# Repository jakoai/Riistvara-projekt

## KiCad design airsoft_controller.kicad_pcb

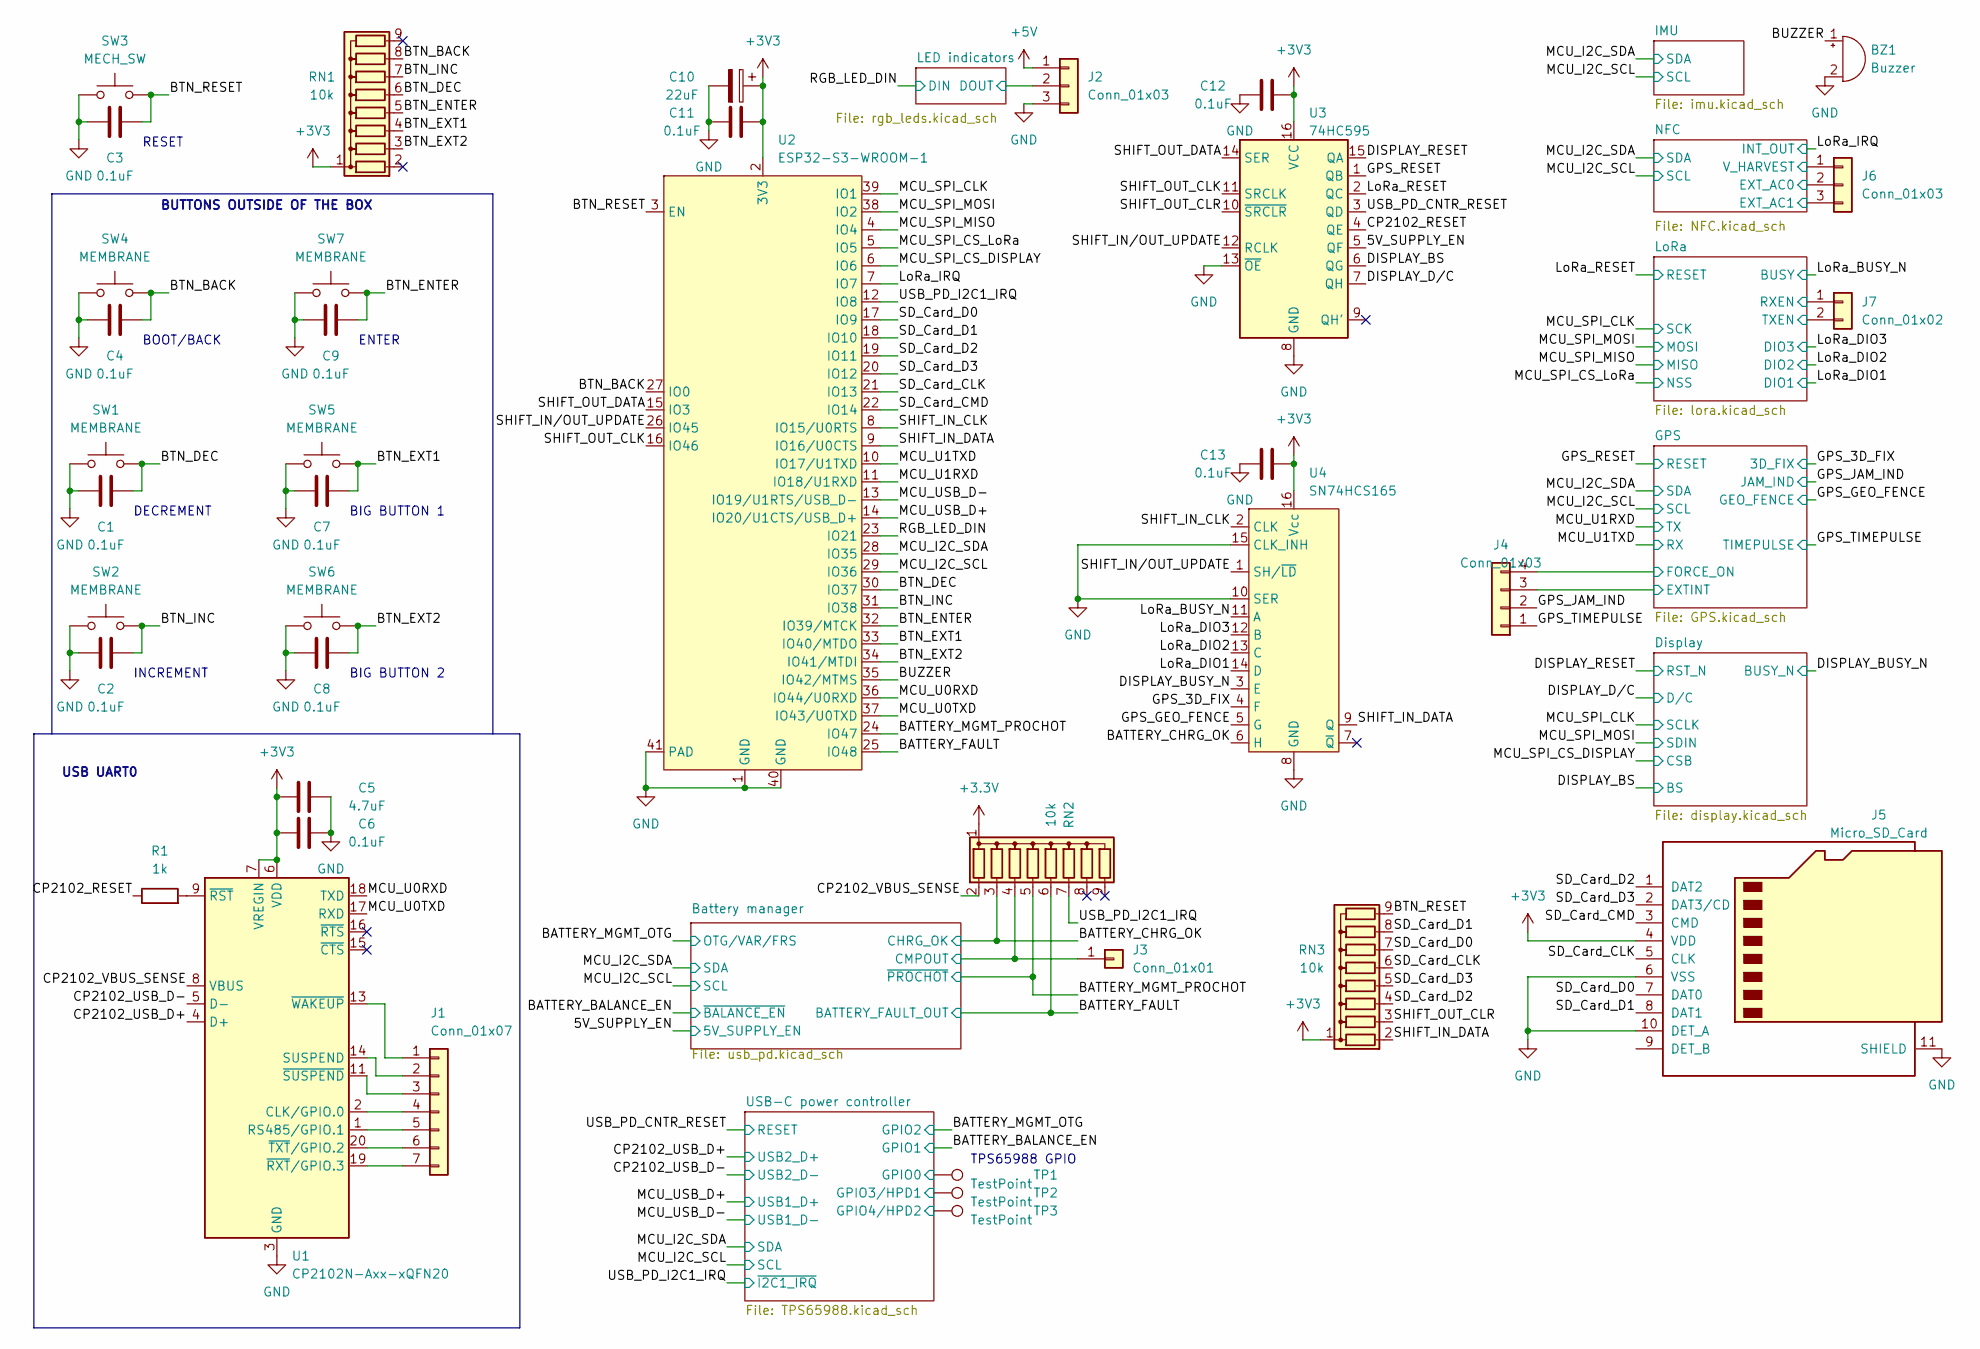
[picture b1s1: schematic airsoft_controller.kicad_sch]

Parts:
BZ1: Buzzer
C1, C2, C3, C4, C6, C7, C8, C9, C11, C12, C13: 0.1uF; C_0603_1608Metric_Pad1.08x0.95mm_HandSolder
C5: 4.7uF; C_0603_1608Metric_Pad1.08x0.95mm_HandSolder
C10: 22uF; CP_Elec_5x5.3
J1: Conn_01x07; PinSocket_1x07_P2.54mm_Vertical
J2, J6: Conn_01x03; PinSocket_1x03_P2.54mm_Vertical
J3: Conn_01x01; PinSocket_1x01_P2.54mm_Vertical
J4: Conn_01x03; PinSocket_1x04_P2.54mm_Vertical
J5: Micro_SD_Card; microSD-W3JA7HH800293
J7: Conn_01x02; PinSocket_1x02_P2.54mm_Vertical
R1: 1k; R_0603_1608Metric_Pad0.98x0.95mm_HandSolder
RN1, RN2, RN3: 10k; R_Array_SIP9
SW1, SW2, SW4, SW5, SW6, SW7: MEMBRANE; SW_rubber_membrane_for_led
SW3: MECH_SW; SWITCH_TL3315NF250Q
TP1, TP2, TP3: TestPoint; TestPoint_Pad_D1.5mm
U1: CP2102N-Axx-xQFN20; SiliconLabs_QFN-20-1EP_3x3mm_P0.5mm_EP1.8x1.8mm
U2: ESP32-S3-WROOM-1; ESP32­S3­WROOM­1
U3: 74HC595; TSSOP-16_4.4x5mm_P0.65mm
U4: SN74HCS165; TSSOP-16_4.4x5mm_P0.65mm

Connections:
+3V3: C5.1, C6.1, C10.1, C11.2, C12.2, C13.2, J5.4 (VDD), RN1.1 (common), RN3.1 (common), U1.6 (VDD), U1.7 (VREGIN), U2.2 (3V3), U3.16 (VCC), U4.16 (Vcc); also elsewhere on the board
+5V: J2.1; also elsewhere on the board
/5V_SUPPLY_EN: U3.5 (QF); also elsewhere on the board
/BATTERY_CHRG_OK: RN2.3 (R2), U4.6 (H); also elsewhere on the board
/BATTERY_FAULT: RN2.6 (R5), U2.25 (IO48); also elsewhere on the board
/BATTERY_MGMT_PROCHOT: RN2.5 (R4), U2.24 (IO47); also elsewhere on the board
/BTN_BACK: C4.1, RN1.8 (R7), SW4.2, U2.27 (IO0)
/BTN_DEC: C1.1, RN1.6 (R5), SW1.2, U2.30 (IO37)
/BTN_ENTER: C9.1, RN1.5 (R4), SW7.2, U2.32 (IO39/MTCK)
/BTN_EXT1: C7.1, RN1.4 (R3), SW5.2, U2.33 (IO40/MTDO)
/BTN_EXT2: C8.1, RN1.3 (R2), SW6.2, U2.34 (IO41/MTDI)
/BTN_INC: C2.1, RN1.7 (R6), SW2.2, U2.31 (IO38)
/BTN_RESET: C3.1, RN3.9 (R8), SW3.3 (B), SW3.4 (B), U2.3 (EN)
/BUZZER: BZ1.1 (-), U2.35 (IO42/MTMS)
/Battery manager/CMPOUT: J3.1, RN2.4 (R3); also elsewhere on the board
/CP2102_RESET: R1.1, U3.4 (QE)
/CP2102_USB_D+: U1.4 (D+); also elsewhere on the board
/CP2102_USB_D-: U1.5 (D-); also elsewhere on the board
/CP2102_VBUS_SENSE: RN2.2 (R1), U1.8 (VBUS)
/DISPLAY_BS: U3.6 (QG); also elsewhere on the board
/DISPLAY_BUSY_N: U4.3 (E); also elsewhere on the board
/DISPLAY_D/C: U3.7 (QH); also elsewhere on the board
/DISPLAY_RESET: U3.15 (QA); also elsewhere on the board
/GPS/EXTINT: J4.3; also elsewhere on the board
/GPS/FORCE_ON: J4.4; also elsewhere on the board
/GPS_3D_FIX: U4.4 (F); also elsewhere on the board
/GPS_GEO_FENCE: U4.5 (G); also elsewhere on the board
/GPS_JAM_IND: J4.2; also elsewhere on the board
/GPS_RESET: U3.1 (QB); also elsewhere on the board
/GPS_TIMEPULSE: J4.1; also elsewhere on the board
/LED indicators/DOUT: J2.2; also elsewhere on the board
/LoRa/RXEN: J7.1; also elsewhere on the board
/LoRa/TXEN: J7.2; also elsewhere on the board
/LoRa_BUSY_N: U4.11 (A); also elsewhere on the board
/LoRa_DIO1: U4.14 (D); also elsewhere on the board
/LoRa_DIO2: U4.13 (C); also elsewhere on the board
/LoRa_DIO3: U4.12 (B); also elsewhere on the board
/LoRa_IRQ: U2.7 (IO7); also elsewhere on the board
/LoRa_RESET: U3.2 (QC); also elsewhere on the board
/MCU_I2C_SCL: U2.29 (IO36); also elsewhere on the board
/MCU_I2C_SDA: U2.28 (IO35); also elsewhere on the board
/MCU_SPI_CLK: U2.39 (IO1); also elsewhere on the board
/MCU_SPI_CS_DISPLAY: U2.6 (IO6); also elsewhere on the board
/MCU_SPI_CS_LoRa: U2.5 (IO5); also elsewhere on the board
/MCU_SPI_MISO: U2.4 (IO4); also elsewhere on the board
/MCU_SPI_MOSI: U2.38 (IO2); also elsewhere on the board
/MCU_U0RXD: U1.18 (TXD), U2.36 (IO44/U0RXD)
/MCU_U0TXD: U1.17 (RXD), U2.37 (IO43/U0TXD)
/MCU_U1RXD: U2.11 (IO18/U1RXD); also elsewhere on the board
/MCU_U1TXD: U2.10 (IO17/U1TXD); also elsewhere on the board
/MCU_USB_D+: U2.14 (IO20/U1CTS/USB_D+); also elsewhere on the board
/MCU_USB_D-: U2.13 (IO19/U1RTS/USB_D-); also elsewhere on the board
/NFC/EXT_AC0: J6.2; also elsewhere on the board
/NFC/EXT_AC1: J6.3; also elsewhere on the board
/NFC/V_HARVEST: J6.1; also elsewhere on the board
/RGB_LED_DIN: U2.23 (IO21); also elsewhere on the board
/SD_Card_CLK: J5.5 (CLK), RN3.6 (R5), U2.21 (IO13)
/SD_Card_CMD: J5.3 (CMD), U2.22 (IO14)
/SD_Card_D0: J5.7 (DAT0), RN3.7 (R6), U2.17 (IO9)
/SD_Card_D1: J5.8 (DAT1), RN3.8 (R7), U2.18 (IO10)
/SD_Card_D2: J5.1 (DAT2), RN3.4 (R3), U2.19 (IO11)
/SD_Card_D3: J5.2 (DAT3/CD), RN3.5 (R4), U2.20 (IO12)
/SHIFT_IN_CLK: U2.8 (IO15/U0RTS), U4.2 (CLK)
/SHIFT_IN_DATA: RN3.2 (R1), U2.9 (IO16/U0CTS), U4.9 (Q)
/SHIFT_IN/OUT_UPDATE: U2.26 (IO45), U3.12 (RCLK), U4.1 (SH/~LD)
/SHIFT_OUT_CLK: U2.16 (IO46), U3.11 (SRCLK)
/SHIFT_OUT_CLR: RN3.3 (R2), U3.10 (~SRCLR)
/SHIFT_OUT_DATA: U2.15 (IO3), U3.14 (SER)
/USB-C power controller/GPIO0: TP1.1; also elsewhere on the board
/USB-C power controller/GPIO3/HPD1: TP2.1; also elsewhere on the board
/USB-C power controller/GPIO4/HPD2: TP3.1; also elsewhere on the board
/USB_PD_CNTR_RESET: U3.3 (QD); also elsewhere on the board
/USB_PD_I2C1_IRQ: RN2.7 (R6), U2.12 (IO8); also elsewhere on the board
GND: BZ1.2 (+), C1.2, C2.2, C3.2, C4.2, C5.2, C6.2, C7.2, C8.2, C9.2, C10.2, C11.1, C12.1, C13.1, J2.3, J5.6 (VSS), J5.10 (DET_A), J5.11 (SHIELD), SW1.1, SW2.1, SW3.1 (A), SW3.2 (A), SW4.1, SW5.1, SW6.1, SW7.1, U1.3 (GND), U1.12 (GND), U1.21 (GND), U2.1 (GND), U2.40 (GND), U2.41 (PAD), U3.8 (GND), U3.13 (~OE), U4.8 (GND), U4.10 (SER), U4.15 (CLK_INH); also elsewhere on the board
unnamed: J1.1, U1.13 (~WAKEUP)
unnamed: J1.2, U1.14 (SUSPEND)
unnamed: J1.3, U1.11 (~SUSPEND)
unnamed: J1.4, U1.2 (CLK/GPIO.0)
unnamed: J1.5, U1.1 (RS485/GPIO.1)
unnamed: J1.6, U1.20 (~TXT/GPIO.2)
unnamed: J1.7, U1.19 (~RXT/GPIO.3)
unnamed: R1.2, U1.9 (~RST)

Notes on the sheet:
BOOT/BACK
ENTER
USB UART0
RESET
DECREMENT
INCREMENT
TPS65988 GPIO
BIG BUTTON 1
BUTTONS OUTSIDE OF THE BOX
BIG BUTTON 2

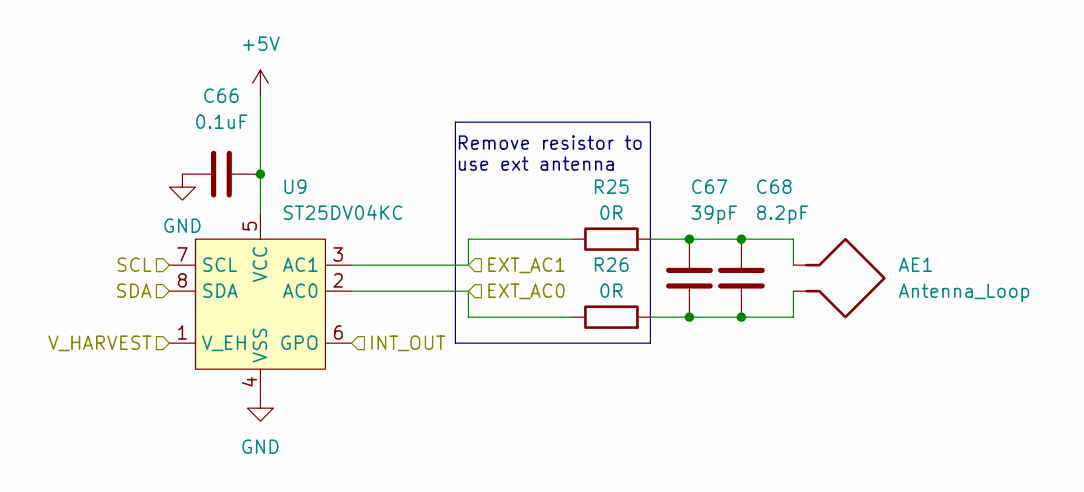
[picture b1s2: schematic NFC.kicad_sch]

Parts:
AE1: Antenna_Loop; Antenna_loop-13.56MHz
C66: 0.1uF; C_0603_1608Metric_Pad1.08x0.95mm_HandSolder
C67: 39pF; C_0603_1608Metric_Pad1.08x0.95mm_HandSolder
C68: 8.2pF; C_0603_1608Metric_Pad1.08x0.95mm_HandSolder
R25, R26: 0R; R_0603_1608Metric_Pad0.98x0.95mm_HandSolder
U9: ST25DV04KC; TSSOP-8_6.4x3mm_P0.65mm

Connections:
+5V: C66.2, U9.5 (VCC); also elsewhere on the board
/LoRa_IRQ: U9.6 (GPO); also elsewhere on the board
/MCU_I2C_SCL: U9.7 (SCL); also elsewhere on the board
/MCU_I2C_SDA: U9.8 (SDA); also elsewhere on the board
/NFC/EXT_AC0: R26.1, U9.2 (AC0); also elsewhere on the board
/NFC/EXT_AC1: R25.1, U9.3 (AC1); also elsewhere on the board
/NFC/V_HARVEST: U9.1 (V_EH); also elsewhere on the board
GND: C66.1, U9.4 (VSS); also elsewhere on the board
unnamed: AE1.1, C67.1, C68.1, R25.2
unnamed: AE1.2, C67.2, C68.2, R26.2

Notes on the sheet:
Remove resistor to use ext antenna

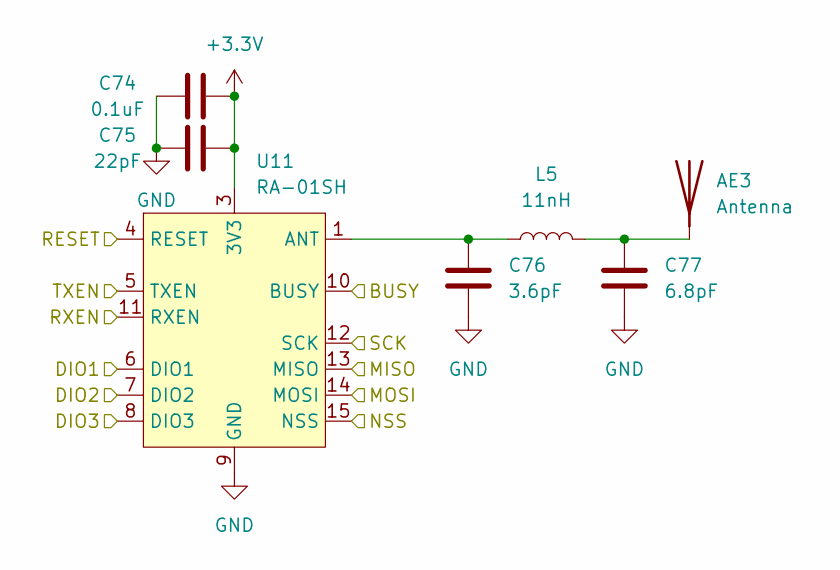
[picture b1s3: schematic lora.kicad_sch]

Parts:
AE3: Antenna; LoRa-antenna-868-HESM
C74: 0.1uF; C_0603_1608Metric_Pad1.08x0.95mm_HandSolder
C75: 22pF; C_0603_1608Metric_Pad1.08x0.95mm_HandSolder
C76: 3.6pF; C_0603_1608Metric_Pad1.08x0.95mm_HandSolder
C77: 6.8pF; C_0603_1608Metric_Pad1.08x0.95mm_HandSolder
L5: 11nH; L_0603_1608Metric_Pad1.05x0.95mm_HandSolder
U11: RA-01SH

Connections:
/LoRa/RXEN: U11.11 (RXEN); also elsewhere on the board
/LoRa/TXEN: U11.5 (TXEN); also elsewhere on the board
/LoRa_BUSY_N: U11.10 (BUSY); also elsewhere on the board
/LoRa_DIO1: U11.6 (DIO1); also elsewhere on the board
/LoRa_DIO2: U11.7 (DIO2); also elsewhere on the board
/LoRa_DIO3: U11.8 (DIO3); also elsewhere on the board
/LoRa_RESET: U11.4 (RESET); also elsewhere on the board
/MCU_SPI_CLK: U11.12 (SCK); also elsewhere on the board
/MCU_SPI_CS_LoRa: U11.15 (NSS); also elsewhere on the board
/MCU_SPI_MISO: U11.13 (MISO); also elsewhere on the board
/MCU_SPI_MOSI: U11.14 (MOSI); also elsewhere on the board
GND: C74.1, C75.1, C76.2, C77.2, U11.2 (GND), U11.9 (GND), U11.16 (GND); also elsewhere on the board
unnamed: AE3.1 (A), C77.1, L5.2
unnamed: C76.1, L5.1, U11.1 (ANT)

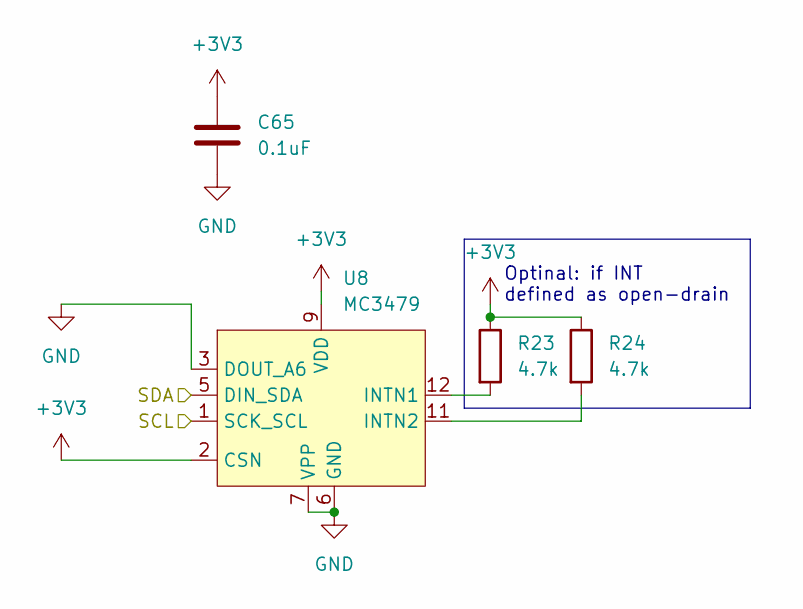
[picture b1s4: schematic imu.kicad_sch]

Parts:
C65: 0.1uF; C_0603_1608Metric_Pad1.08x0.95mm_HandSolder
R23, R24: 4.7k; R_0603_1608Metric_Pad0.98x0.95mm_HandSolder
U8: MC3479; LGA-12_2x2mm_P0.5mm

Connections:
+3V3: C65.2, R23.1, R24.1, U8.2 (CSN), U8.9 (VDD); also elsewhere on the board
/MCU_I2C_SCL: U8.1 (SCK_SCL); also elsewhere on the board
/MCU_I2C_SDA: U8.5 (DIN_SDA); also elsewhere on the board
GND: C65.1, U8.3 (DOUT_A6), U8.6 (GND), U8.7 (VPP); also elsewhere on the board
unnamed: R23.2, U8.12 (INTN1)
unnamed: R24.2, U8.11 (INTN2)

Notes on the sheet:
Optinal: if INT defined as open-drain

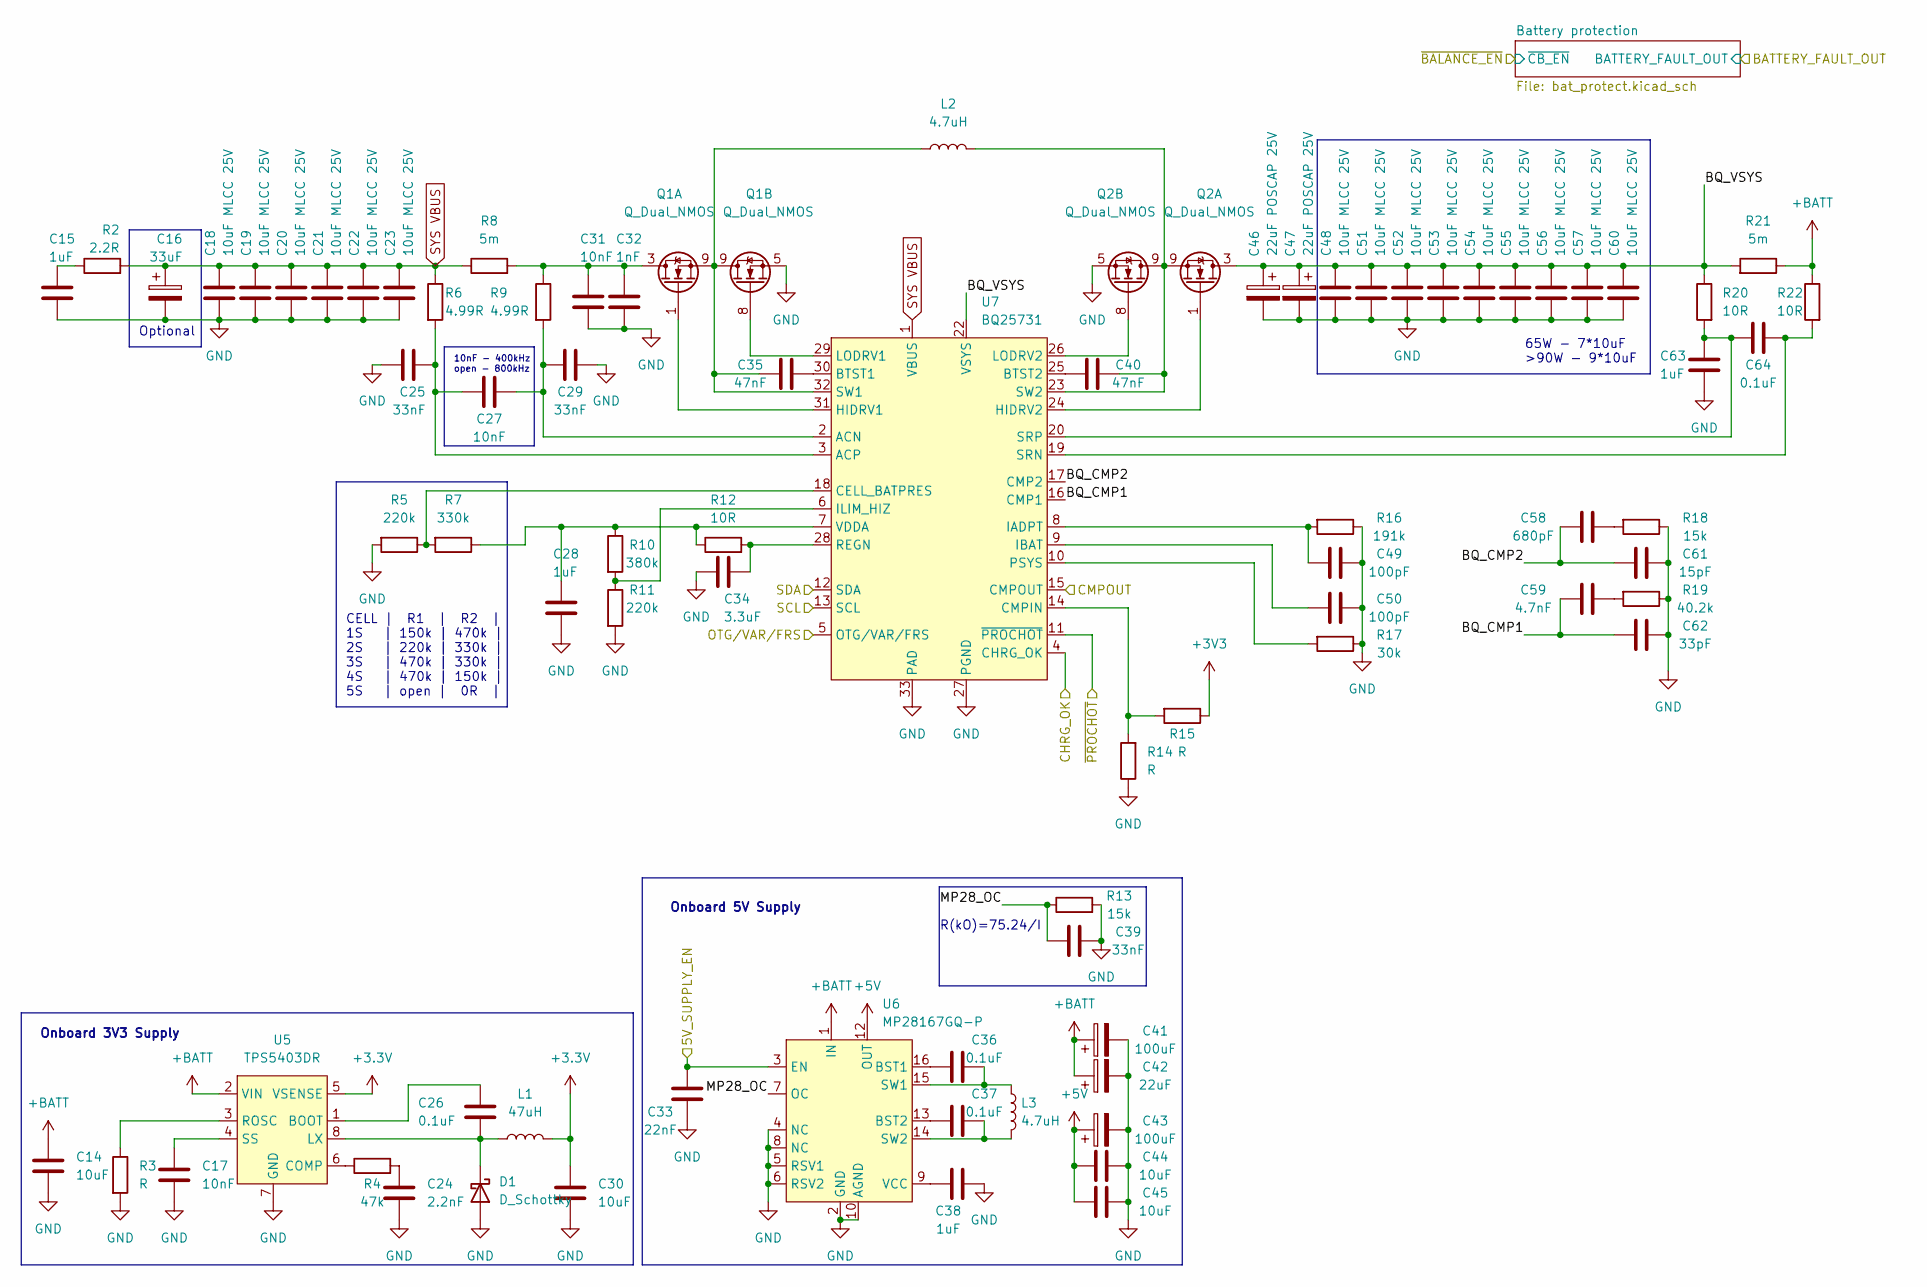
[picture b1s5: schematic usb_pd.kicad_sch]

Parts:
C14, C44, C45: 10uF; C_0805_2012Metric_Pad1.18x1.45mm_HandSolder
C15, C28, C38, C63: 1uF; C_0603_1608Metric_Pad1.08x0.95mm_HandSolder
C16: 33uF; CP_Elec_6.3x5.4
C17, C27, C31: 10nF; C_0603_1608Metric_Pad1.08x0.95mm_HandSolder
C18, C19, C20, C21, C22, C23, C51, C52, C53, C54, C55, C56, C57, C60: 10uF MLCC 25V; C_0805_2012Metric_Pad1.18x1.45mm_HandSolder
C24: 2.2nF; C_0603_1608Metric_Pad1.08x0.95mm_HandSolder
C25, C29, C39: 33nF; C_0603_1608Metric_Pad1.08x0.95mm_HandSolder
C26, C36, C37, C64: 0.1uF; C_0603_1608Metric_Pad1.08x0.95mm_HandSolder
C30: 10uF; C_1206_3216Metric_Pad1.33x1.80mm_HandSolder
C32: 1nF; C_0603_1608Metric_Pad1.08x0.95mm_HandSolder
C33: 22nF; C_0603_1608Metric_Pad1.08x0.95mm_HandSolder
C34: 3.3uF; C_0603_1608Metric_Pad1.08x0.95mm_HandSolder
C35, C40: 47nF; C_0603_1608Metric_Pad1.08x0.95mm_HandSolder
C41, C43: 100uF; CP_Elec_6.3x7.7
C42: 22uF; CP_Elec_5x5.3
C46, C47: 22uF POSCAP 25V; C_1210_3225Metric_Pad1.33x2.70mm_HandSolder
C48: 10uF MLCC 25V; C_1206_3216Metric_Pad1.33x1.80mm_HandSolder
C49, C50: 100pF; C_0603_1608Metric_Pad1.08x0.95mm_HandSolder
C58: 680pF; C_0603_1608Metric_Pad1.08x0.95mm_HandSolder
C59: 4.7nF; C_0603_1608Metric_Pad1.08x0.95mm_HandSolder
C61: 15pF; C_0603_1608Metric_Pad1.08x0.95mm_HandSolder
C62: 33pF; C_0603_1608Metric_Pad1.08x0.95mm_HandSolder
D1: D_Schottky; D_SMB
L1: 47uH; Inductor_104CDMCC
L2: 4.7uH; Inductor_SRP1265C
L3: 4.7uH; Inductor_WLPMA0A040
Q1, Q2: Q_Dual_NMOS; Q_DUAL_NMOS_DMT3006LPB
R2: 2.2R; R_0603_1608Metric_Pad0.98x0.95mm_HandSolder
R3, R14, R15: R; R_0603_1608Metric_Pad0.98x0.95mm_HandSolder
R4: 47k; R_0603_1608Metric_Pad0.98x0.95mm_HandSolder
R5, R11: 220k; R_0603_1608Metric_Pad0.98x0.95mm_HandSolder
R6, R9: 4.99R; R_0603_1608Metric_Pad0.98x0.95mm_HandSolder
R7: 330k; R_0603_1608Metric_Pad0.98x0.95mm_HandSolder
R8, R21: 5m; R_0612_1632Metric_Pad1.18x3.40mm_HandSolder
R10: 380k; R_0603_1608Metric_Pad0.98x0.95mm_HandSolder
R12, R20, R22: 10R; R_0603_1608Metric_Pad0.98x0.95mm_HandSolder
R13, R18: 15k; R_0603_1608Metric_Pad0.98x0.95mm_HandSolder
R16: 191k; R_0603_1608Metric_Pad0.98x0.95mm_HandSolder
R17: 30k; R_0603_1608Metric_Pad0.98x0.95mm_HandSolder
R19: 40.2k; R_0603_1608Metric_Pad0.98x0.95mm_HandSolder
U5: TPS5403DR; SOIC-8_3.9x4.9mm_P1.27mm
U6: MP28167GQ-P; QFN-16
U7: BQ25731; Texas_S-PWQFN-N32_EP2.8x2.8mm

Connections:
+5V: C43.1, C44.1, C45.1, U6.12 (OUT); also elsewhere on the board
+BATT: C14.2, C41.1, C42.1, R21.1, R22.1, U5.2 (VIN), U6.1 (IN); also elsewhere on the board
/5V_SUPPLY_EN: C33.2, U6.3 (EN); also elsewhere on the board
/BATTERY_CHRG_OK: U7.4 (CHRG_OK); also elsewhere on the board
/BATTERY_MGMT_OTG: U7.5 (OTG/VAR/FRS); also elsewhere on the board
/BATTERY_MGMT_PROCHOT: U7.11 (~PROCHOT); also elsewhere on the board
/Battery manager/BQ_CMP1: C59.1, C62.1, U7.16 (CMP1)
/Battery manager/BQ_CMP2: C58.1, C61.1, U7.17 (CMP2)
/Battery manager/BQ_VSYS: C46.1, C47.1, C48.2, C51.2, C52.2, C53.2, C54.2, C55.2, C56.2, C57.2, C60.2, Q2.2 (D1), Q2.3 (D1), Q2.4 (D1), R20.1, R21.2, U7.22 (VSYS)
/Battery manager/CMPOUT: U7.15 (CMPOUT); also elsewhere on the board
/Battery manager/MP28_OC: C39.1, R13.1, U6.7 (OC)
/MCU_I2C_SCL: U7.13 (SCL); also elsewhere on the board
/MCU_I2C_SDA: U7.12 (SDA); also elsewhere on the board
GND: C14.1, C15.1, C16.2, C17.2, C18.1, C19.1, C20.1, C21.1, C22.1, C23.1, C24.2, C25.2, C28.1, C29.2, C30.1, C31.1, C32.1, C33.1, C34.1, C38.2, C39.2, C41.2, C42.2, C43.2, C44.2, C45.2, C46.2, C47.2, C48.1, C49.2, C50.1, C51.1, C52.1, C53.1, C54.1, C55.1, C56.1, C57.1, C60.1, C61.2, C62.2, C63.2, D1.2 (A), Q1.5 (S2), Q1.6 (S2), Q1.7 (S2), Q2.5 (S2), Q2.6 (S2), Q2.7 (S2), R3.2, R5.2, R11.2, R13.2, R14.1, R16.1, R17.1, R18.1, R19.1, U5.7 (GND), U6.2 (GND), U6.4 (NC), U6.5 (RSV1), U6.6 (RSV2), U6.8 (NC), U6.10 (AGND), U6.11 (GND), U7.27 (PGND), U7.33 (PAD); also elsewhere on the board
unnamed: C15.2, R2.1
unnamed: C17.1, U5.4 (SS)
unnamed: C24.1, R4.2
unnamed: C25.1, C27.1, R6.2, U7.3 (ACP)
unnamed: C26.1, U5.1 (BOOT)
unnamed: C26.2, D1.1 (K), L1.1, U5.8 (LX)
unnamed: C27.2, C29.1, R9.2, U7.2 (ACN)
unnamed: C28.2, R7.1, R10.1, R12.1, U7.7 (VDDA)
unnamed: C31.2, C32.2, Q1.2 (D1), Q1.3 (D1), Q1.4 (D1), R8.2, R9.1
unnamed: C34.2, R12.2, U7.28 (REGN)
unnamed: C35.1, U7.30 (BTST1)
unnamed: C35.2, L2.1, Q1.9 (S1/D2), U7.32 (SW1)
unnamed: C36.1, U6.16 (BST1)
unnamed: C36.2, L3.1, U6.15 (SW1)
unnamed: C37.1, U6.13 (BST2)
unnamed: C37.2, L3.2, U6.14 (SW2)
unnamed: C38.1, U6.9 (VCC)
unnamed: C40.1, U7.25 (BTST2)
unnamed: C40.2, L2.2, Q2.9 (S1/D2), U7.23 (SW2)
unnamed: C49.1, R16.2, U7.8 (IADPT)
unnamed: C50.2, U7.9 (IBAT)
unnamed: C58.2, R18.2
unnamed: C59.2, R19.2
unnamed: C63.1, C64.2, R20.2, U7.20 (SRP)
unnamed: C64.1, R22.2, U7.19 (SRN)
unnamed: Q1.1 (G1), U7.31 (HIDRV1)
unnamed: Q1.8 (G2), U7.29 (LODRV1)
unnamed: Q2.1 (G1), U7.24 (HIDRV2)
unnamed: Q2.8 (G2), U7.26 (LODRV2)
unnamed: R3.1, U5.3 (ROSC)
unnamed: R4.1, U5.6 (COMP)
unnamed: R5.1, R7.2, U7.18 (CELL_BATPRES)
unnamed: R10.2, R11.1, U7.6 (ILIM_HIZ)
unnamed: R14.2, R15.2, U7.14 (CMPIN)
unnamed: R17.2, U7.10 (PSYS)
SYS VBUS: C16.1, C18.2, C19.2, C20.2, C21.2, C22.2, C23.2, R2.2, R6.1, R8.1, U7.1 (VBUS); also elsewhere on the board

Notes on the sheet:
65W - 7*10uF >90W - 9*10uF
CELL | R1 | R2 | 1S | 150k | 470k | 2S | 220k | 330k | 3S | 470k | 330k | 4S | 470k | 150k | 5S | open | 0R |
R(kO)=75.24/I
Onboard 3V3 Supply
Optional
10nF - 400kHz open - 800kHz
Onboard 5V Supply

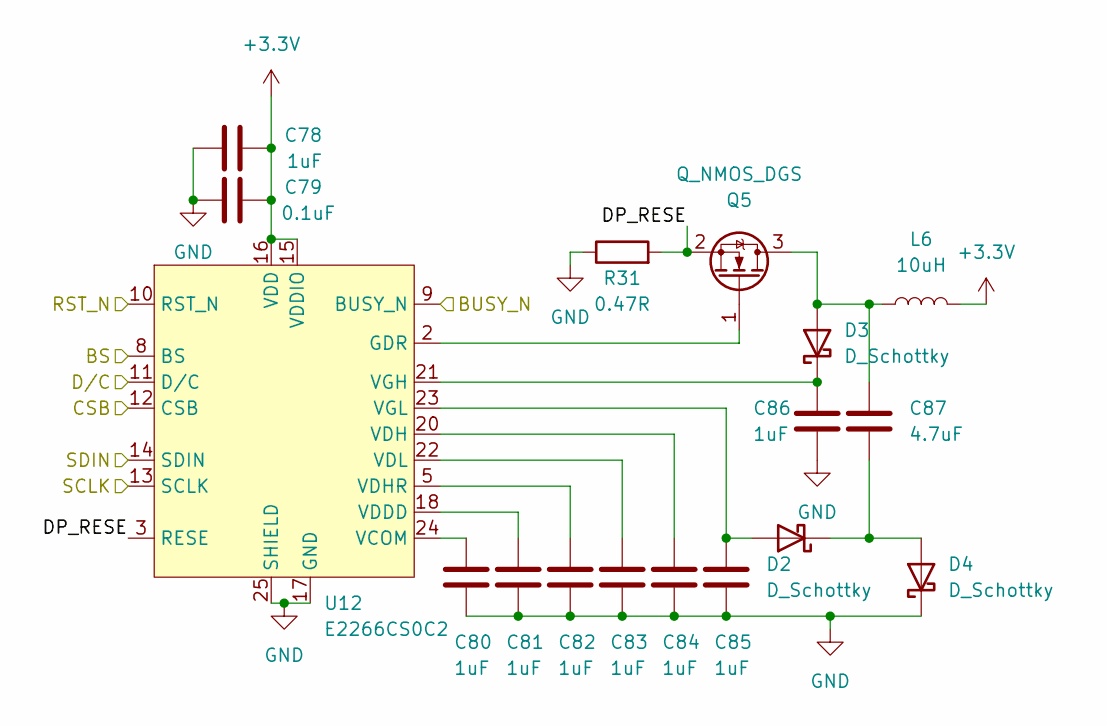
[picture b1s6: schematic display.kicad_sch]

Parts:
C78, C80, C81, C82, C83, C84, C85, C86: 1uF; C_0603_1608Metric_Pad1.08x0.95mm_HandSolder
C79: 0.1uF; C_0603_1608Metric_Pad1.08x0.95mm_HandSolder
C87: 4.7uF; C_0603_1608Metric_Pad1.08x0.95mm_HandSolder
D2, D3, D4: D_Schottky; D-US2H-2
L6: 10uH; L_1210_3225Metric_Pad1.42x2.65mm_HandSolder
Q5: Q_NMOS_DGS; SOT-23
R31: 0.47R; R_0603_1608Metric_Pad0.98x0.95mm_HandSolder
U12: E2266CS0C2; FPC-24p-0.5

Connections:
/DISPLAY_BS: U12.8 (BS); also elsewhere on the board
/DISPLAY_BUSY_N: U12.9 (BUSY_N); also elsewhere on the board
/DISPLAY_D/C: U12.11 (D/C); also elsewhere on the board
/DISPLAY_RESET: U12.10 (RST_N); also elsewhere on the board
/Display/DP_RESE: Q5.2 (S), R31.2, U12.3 (RESE)
/MCU_SPI_CLK: U12.13 (SCLK); also elsewhere on the board
/MCU_SPI_CS_DISPLAY: U12.12 (CSB); also elsewhere on the board
/MCU_SPI_MOSI: U12.14 (SDIN); also elsewhere on the board
GND: C78.2, C79.2, C80.1, C81.1, C82.1, C83.1, C84.1, C85.1, C86.1, D4.1 (K), R31.1, U12.17 (GND), U12.25 (SHIELD), U12.26 (SHIELD); also elsewhere on the board
unnamed: C80.2, U12.24 (VCOM)
unnamed: C81.2, U12.18 (VDDD)
unnamed: C82.2, U12.5 (VDHR)
unnamed: C83.2, U12.22 (VDL)
unnamed: C84.2, U12.20 (VDH)
unnamed: C85.2, D2.2 (A), U12.23 (VGL)
unnamed: C86.2, D3.1 (K), U12.21 (VGH)
unnamed: C87.1, D2.1 (K), D4.2 (A)
unnamed: C87.2, D3.2 (A), L6.1, Q5.3 (D)
unnamed: Q5.1 (G), U12.2 (GDR)

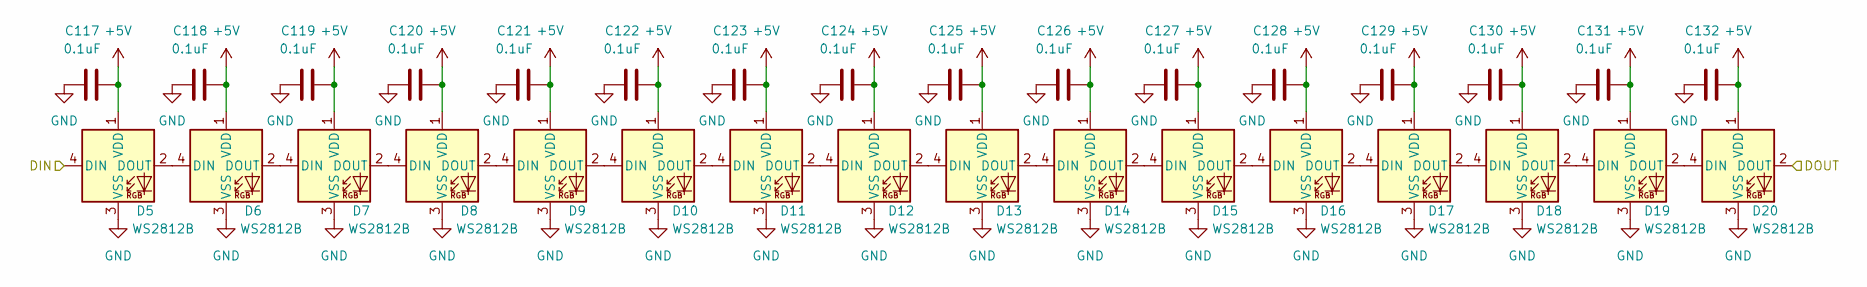
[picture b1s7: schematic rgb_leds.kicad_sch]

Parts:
C117, C118, C119, C120, C121, C122, C123, C124, C125, C126, C127, C128, C129, C130, C131, C132: 0.1uF; C_0603_1608Metric_Pad1.08x0.95mm_HandSolder
D5, D6, D7, D8, D9, D10, D11, D12, D13, D14, D15, D16, D17, D18, D19, D20: WS2812B; LED_WS2812B_PLCC4_5.0x5.0mm_P3.2mm

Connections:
+5V: C117.2, C118.2, C119.2, C120.2, C121.2, C122.2, C123.2, C124.2, C125.2, C126.2, C127.2, C128.2, C129.2, C130.2, C131.2, C132.2, D5.1 (VDD), D6.1 (VDD), D7.1 (VDD), D8.1 (VDD), D9.1 (VDD), D10.1 (VDD), D11.1 (VDD), D12.1 (VDD), D13.1 (VDD), D14.1 (VDD), D15.1 (VDD), D16.1 (VDD), D17.1 (VDD), D18.1 (VDD), D19.1 (VDD), D20.1 (VDD); also elsewhere on the board
/LED indicators/DOUT: D20.2 (DOUT); also elsewhere on the board
/RGB_LED_DIN: D5.4 (DIN); also elsewhere on the board
GND: C117.1, C118.1, C119.1, C120.1, C121.1, C122.1, C123.1, C124.1, C125.1, C126.1, C127.1, C128.1, C129.1, C130.1, C131.1, C132.1, D5.3 (VSS), D6.3 (VSS), D7.3 (VSS), D8.3 (VSS), D9.3 (VSS), D10.3 (VSS), D11.3 (VSS), D12.3 (VSS), D13.3 (VSS), D14.3 (VSS), D15.3 (VSS), D16.3 (VSS), D17.3 (VSS), D18.3 (VSS), D19.3 (VSS), D20.3 (VSS); also elsewhere on the board
unnamed: D5.2 (DOUT), D6.4 (DIN)
unnamed: D6.2 (DOUT), D7.4 (DIN)
unnamed: D7.2 (DOUT), D8.4 (DIN)
unnamed: D8.2 (DOUT), D9.4 (DIN)
unnamed: D10.2 (DOUT), D11.4 (DIN)
unnamed: D9.2 (DOUT), D10.4 (DIN)
unnamed: D11.2 (DOUT), D12.4 (DIN)
unnamed: D12.2 (DOUT), D13.4 (DIN)
unnamed: D13.2 (DOUT), D14.4 (DIN)
unnamed: D14.2 (DOUT), D15.4 (DIN)
unnamed: D15.2 (DOUT), D16.4 (DIN)
unnamed: D16.2 (DOUT), D17.4 (DIN)
unnamed: D17.2 (DOUT), D18.4 (DIN)
unnamed: D19.2 (DOUT), D20.4 (DIN)
unnamed: D18.2 (DOUT), D19.4 (DIN)

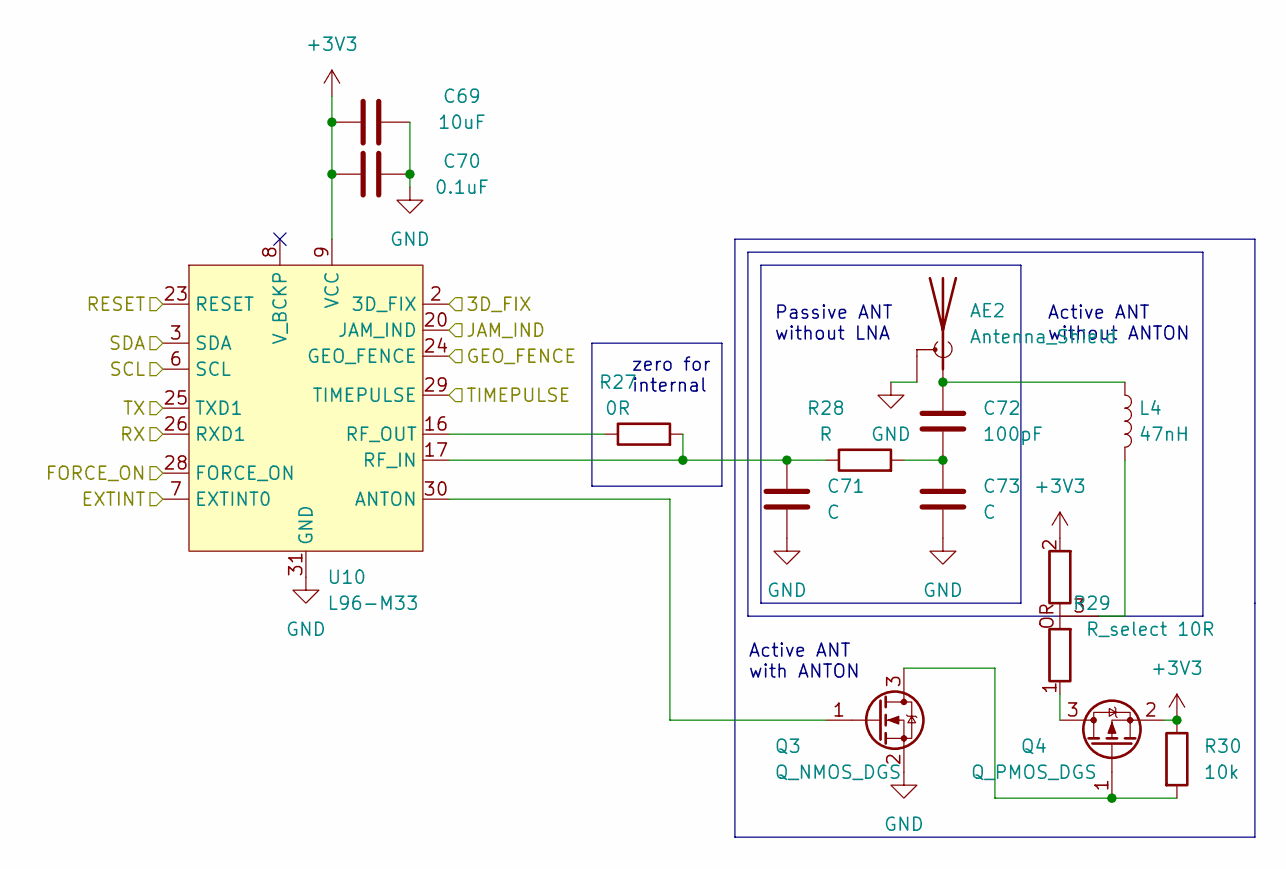
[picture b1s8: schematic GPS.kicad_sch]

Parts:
AE2: Antenna_Shield; U.FL_Molex_MCRF_73412-0110_Vertical
C69: 10uF; C_1206_3216Metric_Pad1.33x1.80mm_HandSolder
C70: 0.1uF; C_0603_1608Metric_Pad1.08x0.95mm_HandSolder
C71, C73: C; C_0603_1608Metric_Pad1.08x0.95mm_HandSolder
C72: 100pF; C_0603_1608Metric_Pad1.08x0.95mm_HandSolder
L4: 47nH; L_0603_1608Metric_Pad1.05x0.95mm_HandSolder
Q3: Q_NMOS_DGS; SOT-23
Q4: Q_PMOS_DGS; SOT-23
R27: 0R; R_0603_1608Metric_Pad0.98x0.95mm_HandSolder
R28: R; R_0603_1608Metric_Pad0.98x0.95mm_HandSolder
R29: R_select 10R; 0603-R-select
R30: 10k; R_0603_1608Metric_Pad0.98x0.95mm_HandSolder
U10: L96-M33; L96

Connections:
+3V3: C69.2, C70.2, Q4.2 (S), R29.2, R30.1, U10.9 (VCC); also elsewhere on the board
/GPS/EXTINT: U10.7 (EXTINT0); also elsewhere on the board
/GPS/FORCE_ON: U10.28 (FORCE_ON); also elsewhere on the board
/GPS_3D_FIX: U10.2 (3D_FIX); also elsewhere on the board
/GPS_GEO_FENCE: U10.24 (GEO_FENCE); also elsewhere on the board
/GPS_JAM_IND: U10.20 (JAM_IND); also elsewhere on the board
/GPS_RESET: U10.23 (RESET); also elsewhere on the board
/GPS_TIMEPULSE: U10.29 (TIMEPULSE); also elsewhere on the board
/MCU_I2C_SCL: U10.6 (SCL); also elsewhere on the board
/MCU_I2C_SDA: U10.3 (SDA); also elsewhere on the board
/MCU_U1RXD: U10.25 (TXD1); also elsewhere on the board
/MCU_U1TXD: U10.26 (RXD1); also elsewhere on the board
GND: AE2.2 (Shield), C69.1, C70.1, C71.2, C73.2, Q3.2 (S), U10.4 (GND), U10.5 (GND), U10.10 (GND), U10.11 (GND), U10.12 (GND), U10.13 (GND), U10.14 (GND), U10.15 (GND), U10.18 (GND), U10.19 (GND), U10.21 (GND), U10.22 (GND), U10.27 (GND), U10.31 (GND); also elsewhere on the board
unnamed: AE2.1 (A), C72.2, L4.1
unnamed: C71.1, R27.2, R28.1, U10.17 (RF_IN)
unnamed: C72.1, C73.1, R28.2
unnamed: L4.2, R29.3
unnamed: Q3.1 (G), U10.30 (ANTON)
unnamed: Q3.3 (D), Q4.1 (G), R30.2
unnamed: Q4.3 (D), R29.1
unnamed: R27.1, U10.16 (RF_OUT)

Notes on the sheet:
Active ANT with ANTON
zero for internal
Active ANT without ANTON
Passive ANT without LNA

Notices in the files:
software/main/airsoft_manager.c:
SPDX-FileCopyrightText: 2022 Espressif Systems (Shanghai) CO LTD
SPDX-License-Identifier: Unlicense OR CC0-1.0
